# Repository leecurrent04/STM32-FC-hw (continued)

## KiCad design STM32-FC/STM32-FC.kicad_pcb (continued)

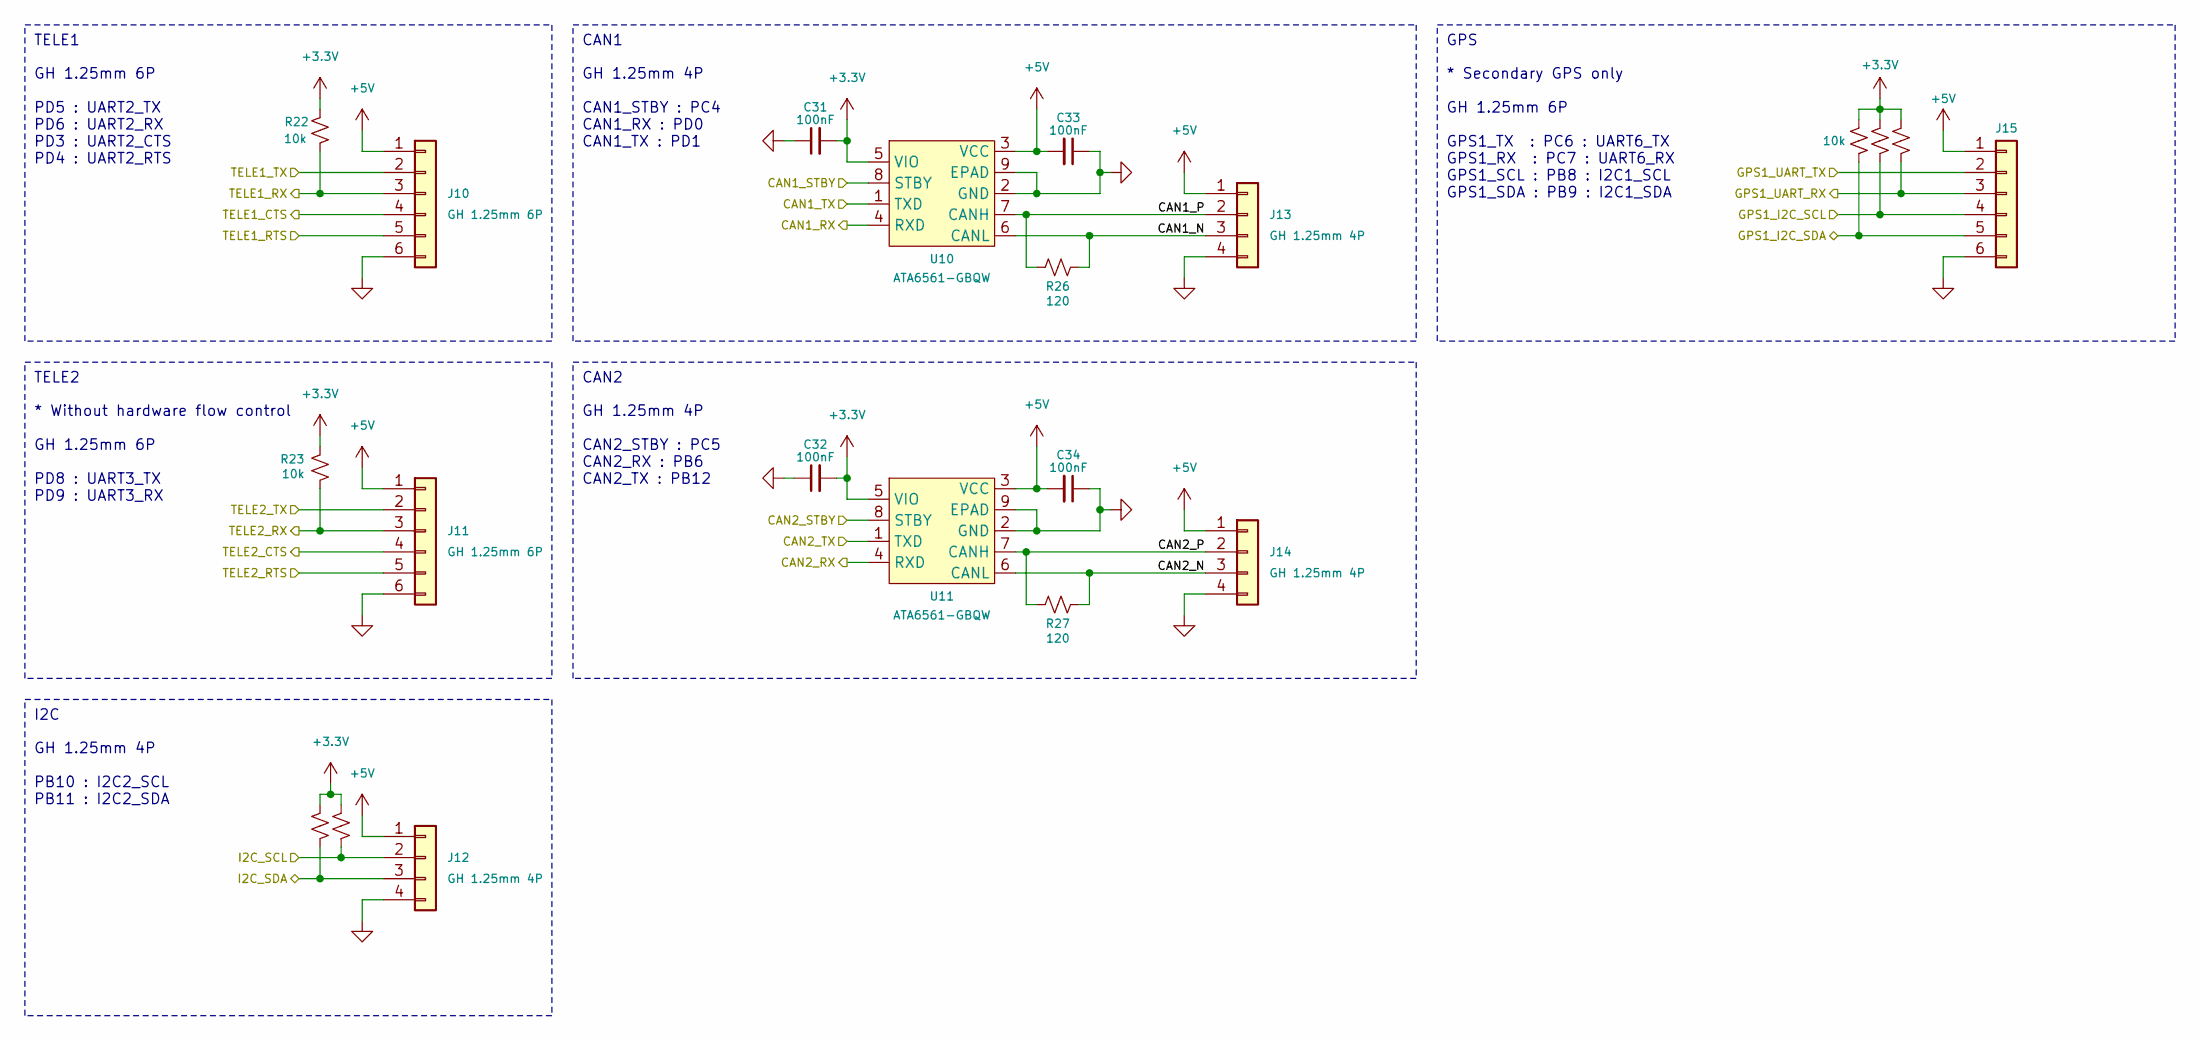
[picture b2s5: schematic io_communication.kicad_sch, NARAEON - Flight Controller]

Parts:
C31, C32, C33, C34: 100nF; C_0402_1005Metric; LCSC C1525
J10, J11, J15: GH 1.25mm 6P; JST_GH_BM06B-GHS-TBT_1x06-1MP_P1.25mm_Vertical; LCSC C189892
J12, J13, J14: GH 1.25mm 4P; JST_GH_BM04B-GHS-TBT_1x04-1MP_P1.25mm_Vertical; LCSC C161692
R22, R23, R24, R25, R28, R29, R30: 10k; R_0402_1005Metric; LCSC C25531
R26, R27: 120; R_0402_1005Metric; LCSC C25079
U10, U11: ATA6561-GBQW; VDFN8_3X3_MCH-L; LCSC C617297

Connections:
+3.3V: C31.2, C32.2, R22.1, R23.1, R24.1, R25.1, R28.1, R29.1, R30.1, U10.5 (VIO), U11.5 (VIO); also elsewhere on the board
+5V: C33.2, C34.2, J10.1, J11.1, J12.1, J13.1, J14.1, J15.1, U10.3 (VCC), U11.3 (VCC); also elsewhere on the board
/CAN1_RX: U10.4 (RXD); also elsewhere on the board
/CAN1_STBY: U10.8 (STBY); also elsewhere on the board
/CAN1_TX: U10.1 (TXD); also elsewhere on the board
/CAN2_RX: U11.4 (RXD); also elsewhere on the board
/CAN2_STBY: U11.8 (STBY); also elsewhere on the board
/CAN2_TX: U11.1 (TXD); also elsewhere on the board
/Communication/CAN1_N: J13.3, R26.2, U10.6 (CANL)
/Communication/CAN1_P: J13.2, R26.1, U10.7 (CANH)
/Communication/CAN2_N: J14.3, R27.2, U11.6 (CANL)
/Communication/CAN2_P: J14.2, R27.1, U11.7 (CANH)
/Communication/TELE2_CTS: J11.4
/Communication/TELE2_RTS: J11.5
/GPS1_RX: J15.3, R30.2; also elsewhere on the board
/GPS1_SCL: J15.4, R29.2; also elsewhere on the board
/GPS1_SDA: J15.5, R28.2; also elsewhere on the board
/GPS1_TX: J15.2; also elsewhere on the board
/I2C1_SCL: J12.2, R25.2; also elsewhere on the board
/I2C1_SDA: J12.3, R24.2; also elsewhere on the board
/UART2_CTS: J10.4; also elsewhere on the board
/UART2_RTS: J10.5; also elsewhere on the board
/UART2_RX: J10.3, R22.2; also elsewhere on the board
/UART2_TX: J10.2; also elsewhere on the board
/UART3_RX: J11.3, R23.2; also elsewhere on the board
/UART3_TX: J11.2; also elsewhere on the board
GND: C31.1, C32.1, C33.1, C34.1, J10.6, J11.6, J12.4, J13.4, J14.4, J15.6, U10.2 (GND), U10.9 (EPAD), U11.2 (GND), U11.9 (EPAD); also elsewhere on the board

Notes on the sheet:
CAN2
GH 1.25mm 4P CAN2_STBY : PC5 CAN2_RX : PB6 CAN2_TX : PB12
GH 1.25mm 4P CAN1_STBY : PC4 CAN1_RX : PD0 CAN1_TX : PD1
TELE1
CAN1
GH 1.25mm 6P PD5 : UART2_TX PD6 : UART2_RX PD3 : UART2_CTS PD4 : UART2_RTS
* Without hardware flow control GH 1.25mm 6P PD8 : UART3_TX PD9 : UART3_RX
I2C
GPS
GH 1.25mm 4P PB10 : I2C2_SCL PB11 : I2C2_SDA
TELE2
* Secondary GPS only GH 1.25mm 6P GPS1_TX : PC6 : UART6_TX GPS1_RX : PC7 : UART6_RX GPS1_SCL : PB8 : I2C1_SCL GPS1_SDA : PB9 : I2C1_SDA

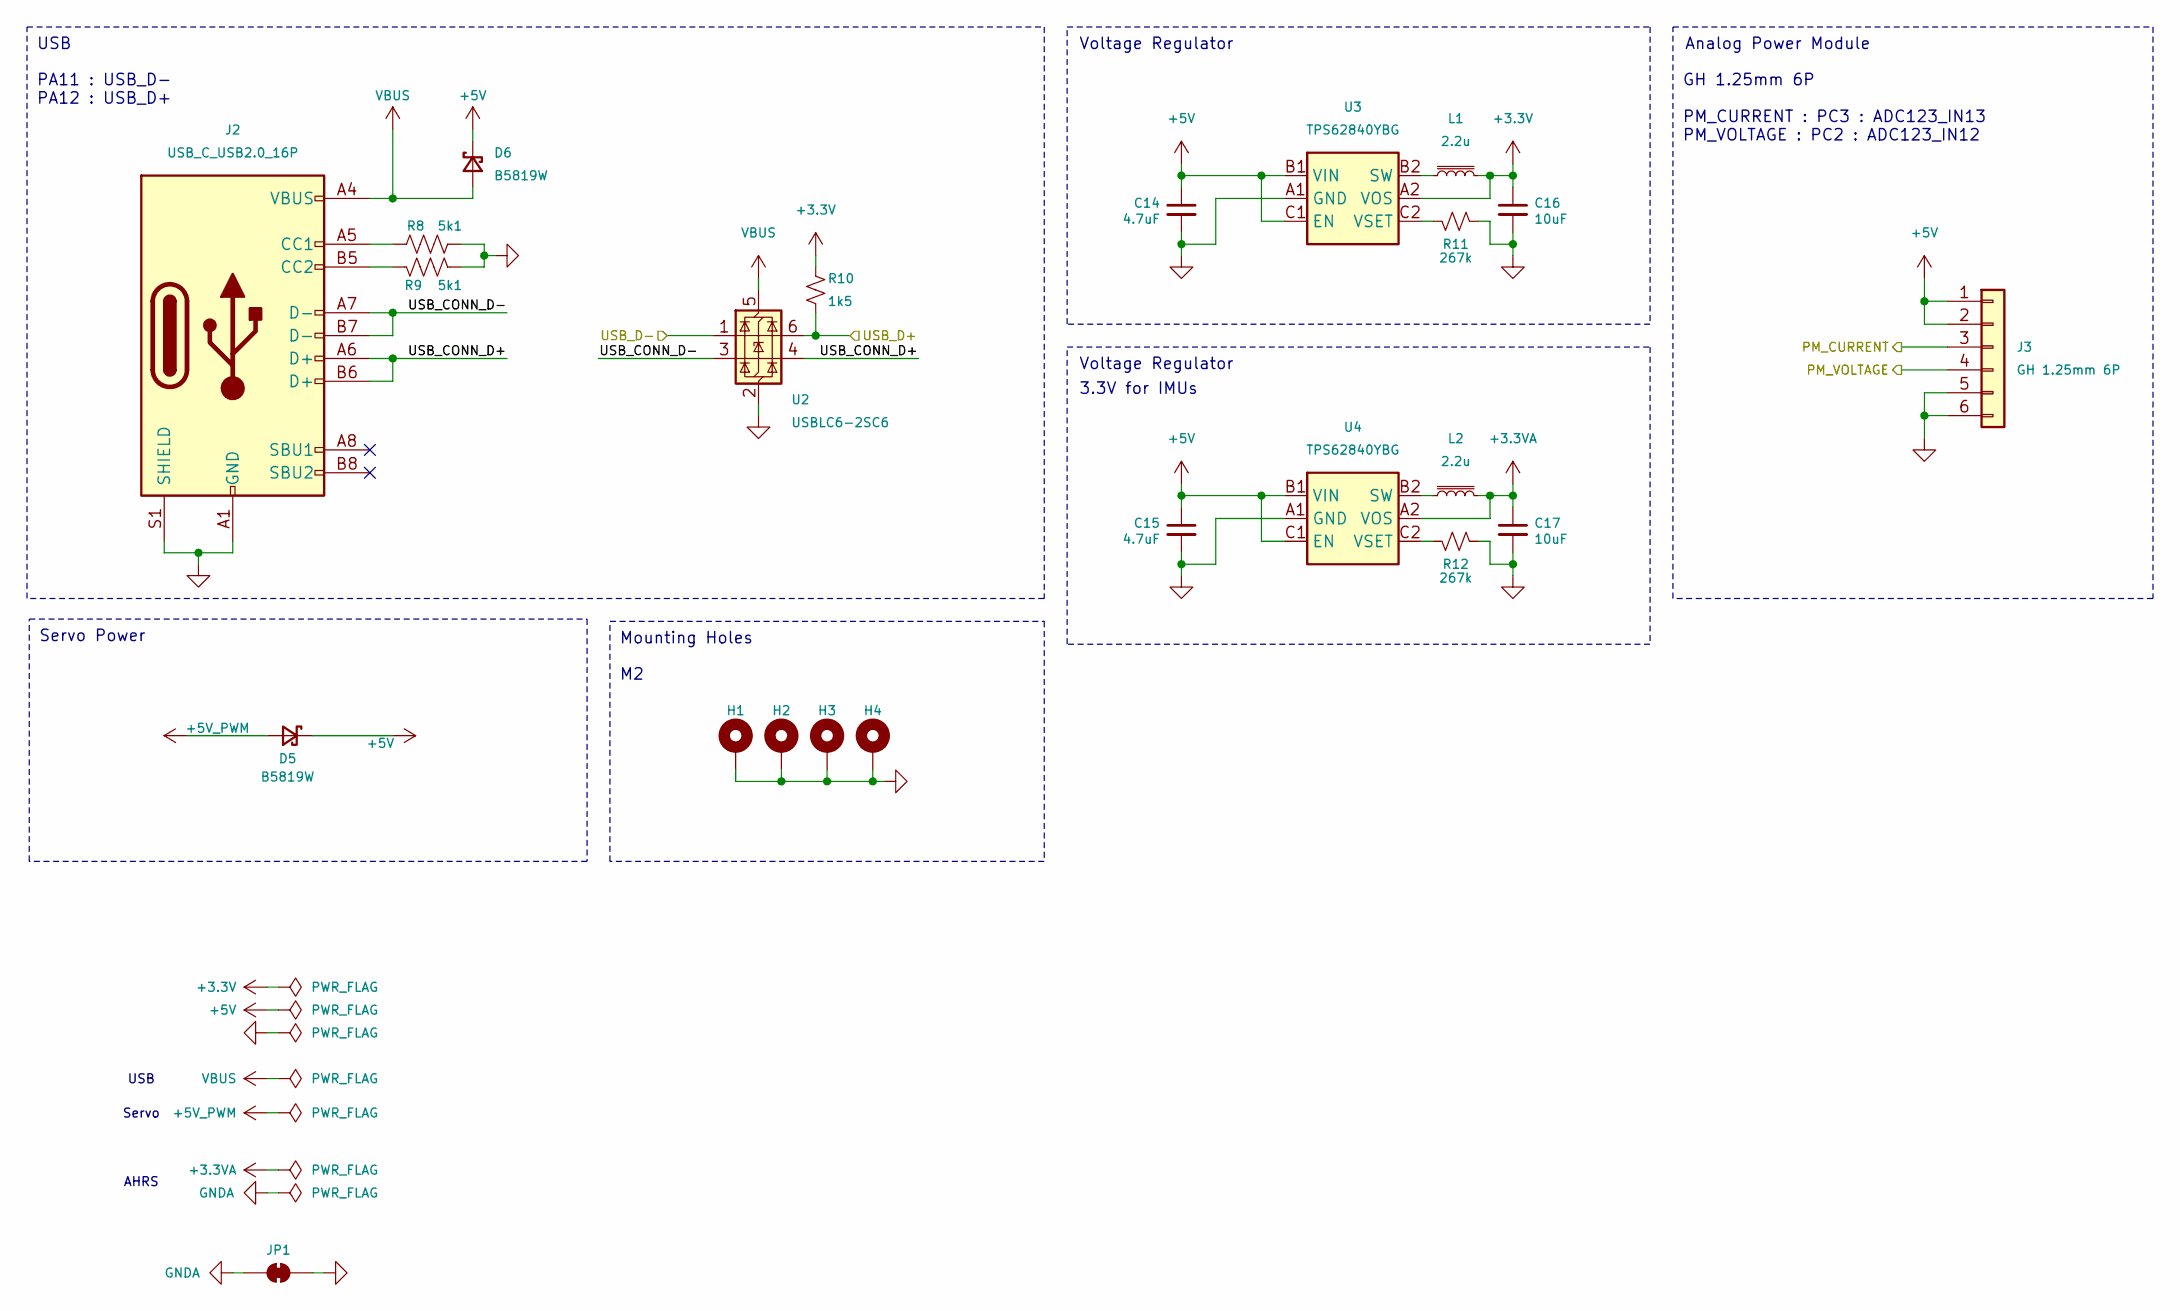
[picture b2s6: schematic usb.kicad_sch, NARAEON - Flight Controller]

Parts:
C14, C15: 4.7uF; C_0402_1005Metric; LCSC C307423
C16, C17: 10uF; C_0402_1005Metric; LCSC C307415
D5, D6: B5819W; D_SOD-323; LCSC C22624
H1, H2, H3, H4: MountingHole; MountingHole_2.2mm_M2_Pad
J2: USB_C_USB2.0_16P; USB_C_Receptacle_GCT_USB4105-xx-A_16P_TopMnt_Horizontal; LCSC C2765186
J3: GH 1.25mm 6P; JST_GH_BM06B-GHS-TBT_1x06-1MP_P1.25mm_Vertical; LCSC C189892
JP1: SolderJumper_2_Bridged; SolderJumper-2_P1.3mm_Bridged_RoundedPad1.0x1.5mm
L1, L2: 2.2u; VLS201610ET-2R2M; LCSC C114768
R8, R9: 5k1; R_0402_1005Metric; LCSC C25905
R10: 1k5; R_0402_1005Metric; LCSC C25867
R11, R12: 267k; R_0402_1005Metric; LCSC C2998050
U2: USBLC6-2SC6; SOT-23-6; LCSC C7519
U3, U4: TPS62840YBG; Texas_DSBGA-6_0.855x1.255mm_Layout2x3_P0.4mm_LevelC; LCSC C2071139

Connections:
+3.3V: C16.1, L1.2, R10.1, U3.A2 (VOS); also elsewhere on the board
+3.3VA: C17.1, L2.2, U4.A2 (VOS); also elsewhere on the board
+5V: C14.1, C15.1, D5.1 (K), D6.1 (K), J3.1, J3.2, U3.B1 (VIN), U3.C1 (EN), U4.B1 (VIN), U4.C1 (EN); also elsewhere on the board
+5V_PWM: D5.2 (A); also elsewhere on the board
/PM_CURRENT: J3.3; also elsewhere on the board
/PM_VOLTAGE: J3.4; also elsewhere on the board
/USB & POWER/USB_CONN_D+: J2.A6 (D+), J2.B6 (D+), U2.4 (I/O2)
/USB & POWER/USB_CONN_D-: J2.A7 (D-), J2.B7 (D-), U2.3 (I/O2)
/USB_D+: R10.2, U2.6 (I/O1); also elsewhere on the board
/USB_D-: U2.1 (I/O1); also elsewhere on the board
GND: C14.2, C15.2, C16.2, C17.2, H1.1, H2.1, H3.1, H4.1, J2.A1 (GND), J2.A12 (GND), J2.B1 (GND), J2.B12 (GND), J2.S1 (SHIELD), J3.5, J3.6, JP1.2 (B), R8.2, R9.2, R11.1, R12.1, U2.2 (GND), U3.A1 (GND), U4.A1 (GND); also elsewhere on the board
GNDA: JP1.1 (A); also elsewhere on the board
unnamed: J2.A5 (CC1), R8.1
unnamed: J2.B5 (CC2), R9.1
unnamed: L1.1, U3.B2 (SW)
unnamed: R11.2, U3.C2 (VSET)
unnamed: L2.1, U4.B2 (SW)
unnamed: R12.2, U4.C2 (VSET)
VBUS: D6.2 (A), J2.A4 (VBUS), J2.A9 (VBUS), J2.B4 (VBUS), J2.B9 (VBUS), U2.5 (VBUS)

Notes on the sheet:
Servo
Voltage Regulator
AHRS
3.3V for IMUs
Mounting Holes
Servo Power
Analog Power Module
GH 1.25mm 6P PM_CURRENT : PC3 : ADC123_IN13 PM_VOLTAGE : PC2 : ADC123_IN12
USB
PA11 : USB_D- PA12 : USB_D+

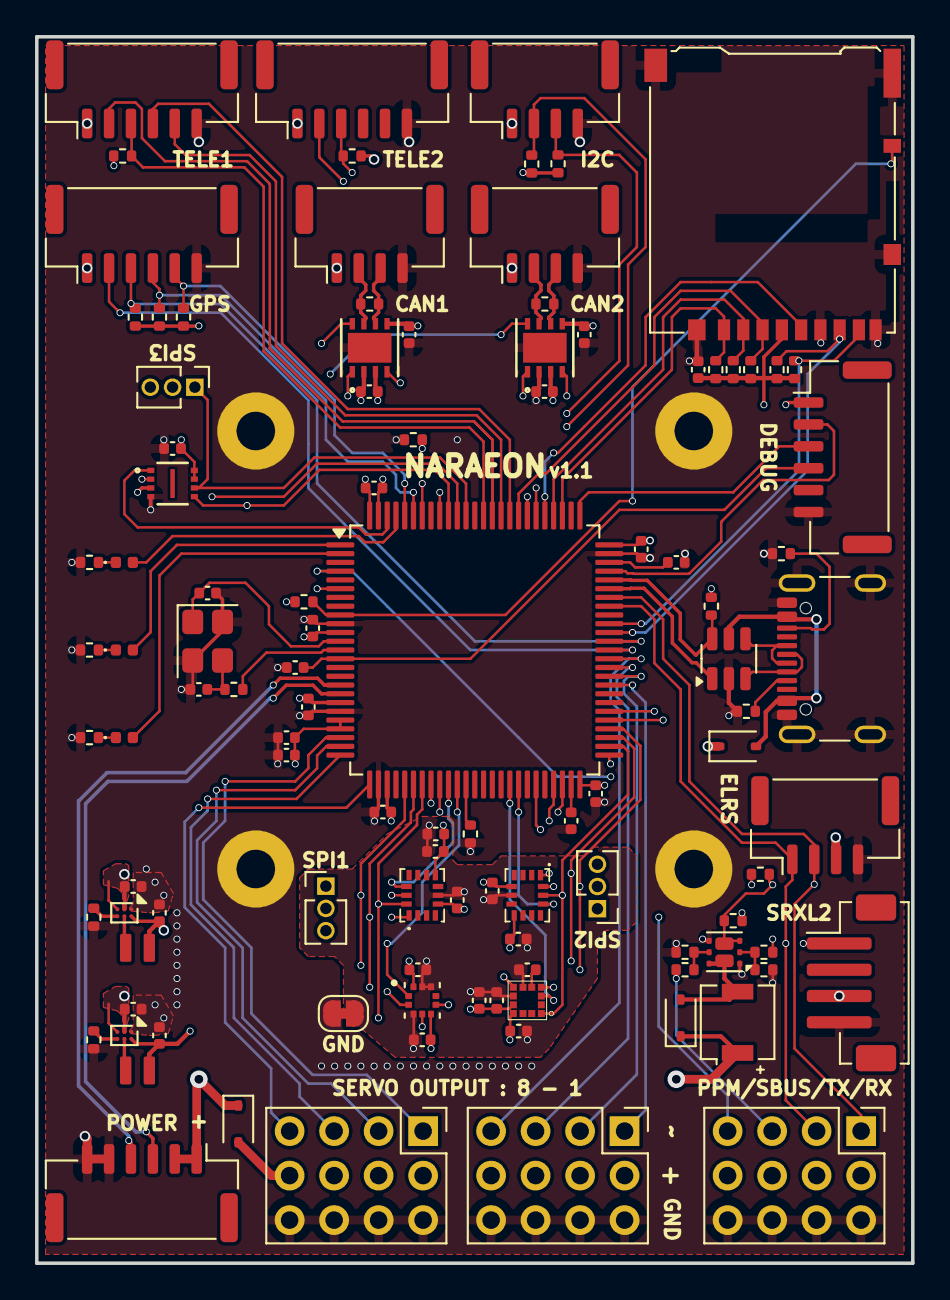
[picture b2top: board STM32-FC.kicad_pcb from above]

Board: 4 copper layers, 50.0 x 70.0 mm, 111 parts (0 on the bottom side), 95 nets.

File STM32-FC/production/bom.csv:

Designator,Footprint,Quantity,Value,LCSC Part #
BZ1,FUET-4020,1,FUET-4020,C391027
"C1, C4",0402,2,10pF,C1545
"C10, C11, C13, C18, C19, C22, C24, C25, C27, C28, C3, C30, C31, C32, C33, C34, C5, C6, C9",0402,19,100nF,C1525
C12,0402,1,1uF,C14445
"C14, C15",0402,2,4.7uF,C307423
"C16, C17, C2, C26",0402,4,10uF,C307415
C20,0402,1,10nF,C15195
C21,0402,1,100pF,C152819
C23,0402,1,2.2nF,C84703
C29,0402,1,220nF,C16651
"C7, C8",0402,2,2.2uF,C170151
D1,0402,1,Red,C130719
"D2, D5, D6",D_SOD-323,3,B5819W,C22624
D3,0402,1,Yellow,C130721
D4,0402,1,Blue,C130724
"J1, J10, J11, J15, J3",JST_GH_BM06B-GHS-TBT_1x06-1MP_P1.25mm_Vertical,5,GH 1.25mm 6P,C189892
"J12, J13, J14, J9",JST_GH_BM04B-GHS-TBT_1x04-1MP_P1.25mm_Vertical,4,GH 1.25mm 4P,C161692
J2,USB_C_Receptacle_GCT_USB4105-xx-A_16P_TopMnt_Horizontal,1,USB_C_USB2.0_16P,C2765186
J4,microSD_HC_Hirose_DM3AT-SF-PEJM5,1,DM3AT-SF-PEJM5,C114218
"J5, J6, J7",PWM_Conn_3x04_JLC,3,PWM_Conn_3x04,C3325573
J8,JST_ZH_B4B-ZR-SM4-TF_1x04-1MP_P1.50mm_Vertical,1,ZH 1.5mm 4P,C485354
"L1, L2",VLS201610ET-2R2M,2,2.2u,C114768
Q1,Nexperia_SOT1118,1,PMDPB30XN,C478009
"R1, R3",0402,2,100k,C25741
R10,0402,1,1k5,C25867
"R11, R12",0402,2,267k,C2998050
"R13, R14, R15, R16, R17, R18, R19, R21, R22, R23, R24, R25, R28, R29, R30, R31, R34",0402,17,10k,C25531
R2,0402,1,4k7,C25900
"R26, R27, R33, R4",0402,4,120, C25079
"R5, R6, R7",0402,3,1k,C11702
"R8, R9",0402,2,5k1,C25905
"TP1, TP2, TP3",PinHeader_1x03_P1.27mm_Vertical,3,Test Pin,C24980
U1,LQFP-100_14x14mm_P0.5mm,1,STM32F407VETx,C28730
"U10, U11",VDFN8_3X3_MCH-L,2,ATA6561-GBQW,C617297
U2,SOT-23-6,1,USBLC6-2SC6,C7519
"U3, U4",Texas_DSBGA-6_0.855x1.255mm_Layout2x3_P0.4mm_LevelC,2,TPS62840YBG,C2071139
U5,USON_LUXIG TR_WIN,1,W25X40CLUXIG,C401661
U6,IIM42352_L,1,ICM-42688-P,C1850418
U7,ICM-45686,1,ICM-45686,C22459454
U8,ICP-20100,1,ICP-20100,C5343527
U9,LIS2MDLTR,1,LIS2MDLRT,C919695
Y1,Crystal_SMD_Abracon_ABM8G-4Pin_3.2x2.5mm,1,16MHz,C1985423

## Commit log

2025-08-05 fix : STM32 USB & VTX
    - USB DM/DP 결선 수정
    - VTX RX/TX 수정
2025-08-09 init:footprint
    footprint 작업 시작
2025-08-12 fix:ATA6561 decap
2025-09-10 fix : BMM350 power 1.8V and add dc2dc converter for 1.8V
2025-09-10 update : BOM and minor fix
    - remove : DC2DC for analog
    - change : JST SM conn. to BM
    - change : ELRS conn. to JST XH (instead of JST SM)
    - update : BOM List
2025-09-10 change : RC size 0402 to 0201
2025-09-10 remove : production files
2025-09-16 v1.0 rollback
2025-09-16 schematic update
2025-09-16 v1.0.1 update WIP
    repactor and USB C bug fix
2025-10-10 schematic update & lib update
    - ICM-45686
    - ICP-20100
    - Micro SD update SDIO instead of SPI
    - servo main output
    - DC2DC buck instead power regulator
2025-10-10 add: servo power & comment
    - Servo power diode add
    - comment update
2025-10-10 update : BJT to MOSFET
2025-10-10 WIP : pcb part layout &* BOM udpate
2025-10-10 update : AHRS PCB layout & routing done
2025-10-10 PCB layout done
2025-10-10 fix : readme & schematic minor fix
    - schematic comment fix
2025-10-10 Update README.md
    by Gemini 2.5 pro
2025-10-11 update : Development board
